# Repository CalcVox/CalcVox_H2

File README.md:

# CalcVox H2 Schematics and PCB Files

[View in Browser](https://kicanvas.org/?github=https://github.com/CalcVox/CalcVox_H2)

This is part of the [CalcVox](https://calcvox.org) Project. I am using KiCAD for these but I have included images below. 

I am trying to make these accessible but am struggling. If you know how to please open an issue.

## Parts

* [Teensy 4.1](https://www.pjrc.com/store/teensy41.html)
* [Seed Studio XIAO ESP32S3](https://www.seeedstudio.com/XIAO-ESP32S3-p-5627.html)
* [Adafruit UDA1334A I2S DAC (using a knockoff from amazon)](https://www.amazon.com/AITRIP-CJMCU-1334-UDA1334A-Decoder-Arduino/dp/B09DG21C7G)
* [Adafruit MiniBoost](https://www.adafruit.com/product/4654)
* [Rotary Encoder](https://www.sparkfun.com/products/9117)
* [Speaker (can use any)](https://www.adafruit.com/product/1891)
* 102AH 2.1mm Barrel Jack
* 3524N 3.5mm Audio Jack
* Piezo Buzzer
* Standard footprint buttons
* Various resistors
* Diodes

## Schematic

## PCB

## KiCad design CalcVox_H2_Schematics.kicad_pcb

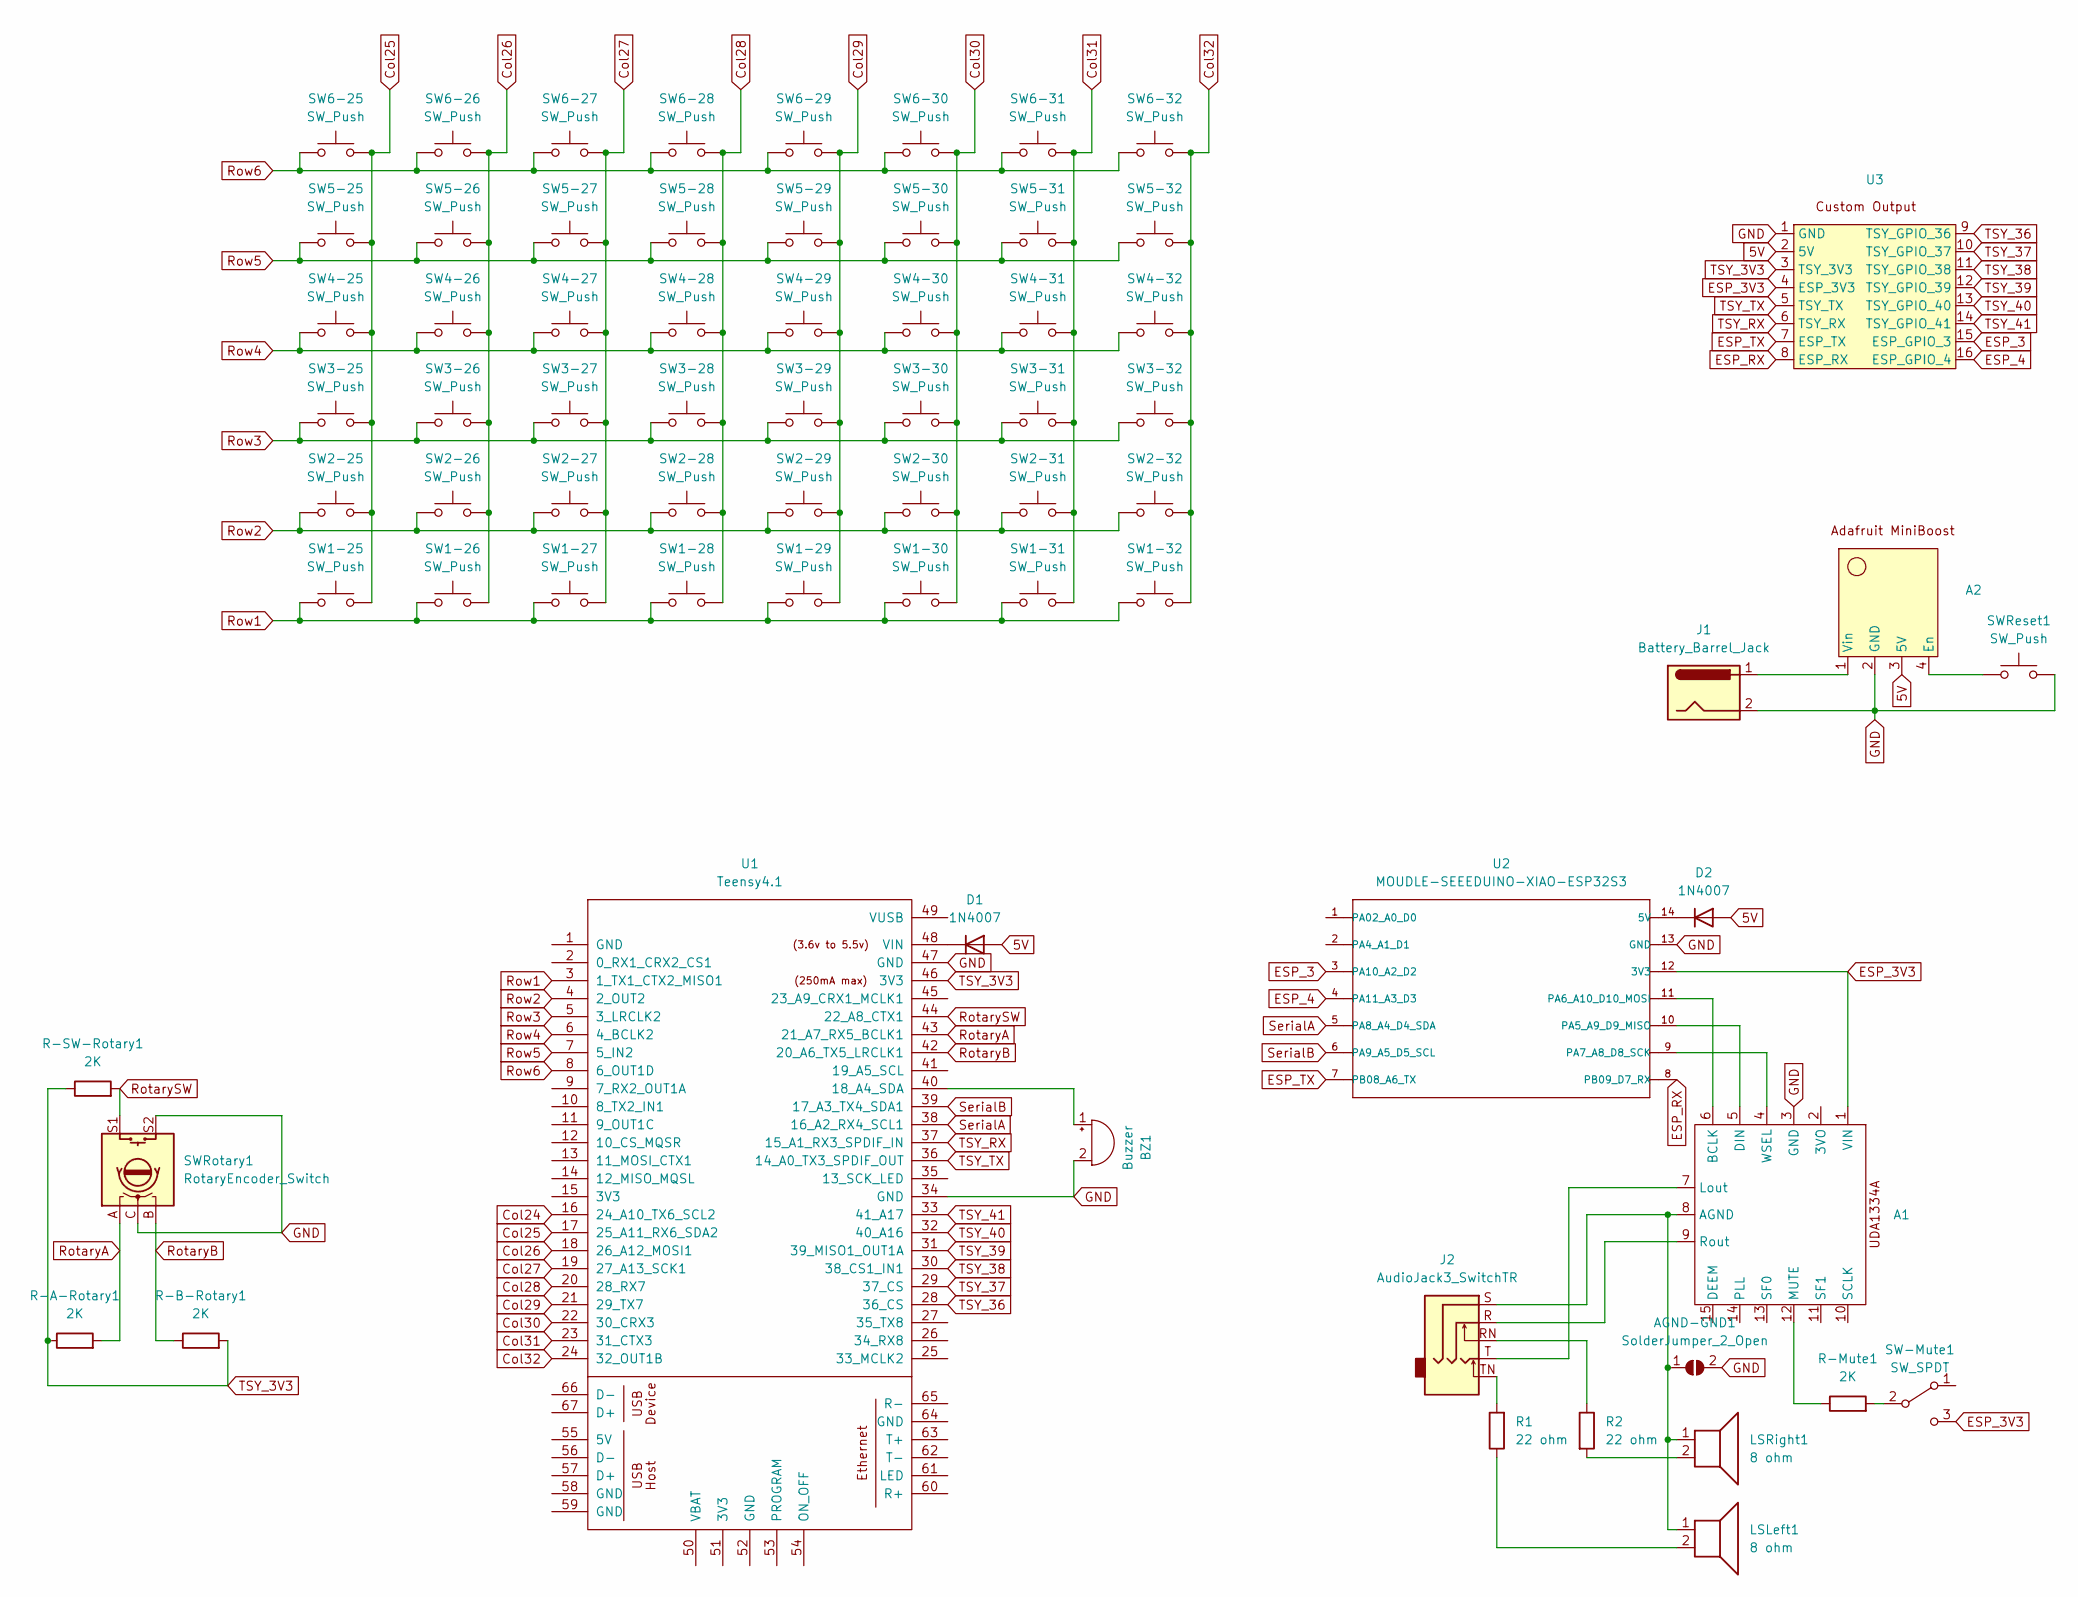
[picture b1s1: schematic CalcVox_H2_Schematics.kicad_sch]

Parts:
A1: Adafruit UDA1334A I2S Stereo DAC
A2: Adafruit MiniBost
AGND-GND1: SolderJumper_2_Open; SolderJumper-2_P1.3mm_Open_TrianglePad1.0x1.5mm
BZ1: Buzzer; Buzzer_12x9.5RM7.6
D1, D2: 1N4007; D_DO-41_SOD81_P10.16mm_Horizontal
J1: Battery_Barrel_Jack; BarrelJack_CUI_PJ-102AH_Horizontal
J2: AudioJack3_SwitchTR; Jack_3.5mm_CUI_SJ1-3524N_Horizontal
LSLeft1: 8 ohm; Speaker Hole
LSRight1: 8 ohm; Speaker Hole
R1, R2: 22 ohm; R_Axial_DIN0617_L17.0mm_D6.0mm_P25.40mm_Horizontal
R-A-Rotary1: 2K; R_Axial_DIN0207_L6.3mm_D2.5mm_P10.16mm_Horizontal
R-B-Rotary1: 2K; R_Axial_DIN0207_L6.3mm_D2.5mm_P10.16mm_Horizontal
R-Mute1: 2K; R_Axial_DIN0207_L6.3mm_D2.5mm_P10.16mm_Horizontal
R-SW-Rotary1: 2K; R_Axial_DIN0207_L6.3mm_D2.5mm_P10.16mm_Horizontal
SW1-25, SW1-26, SW1-27, SW1-28, SW1-29, SW1-30, SW1-31, SW1-32, SW2-25, SW2-26, SW2-27, SW2-28, SW2-29, SW2-30, SW2-31, SW2-32, SW3-25, SW3-26, SW3-27, SW3-28, SW3-29, SW3-30, SW3-31, SW3-32, SW4-25, SW4-26, SW4-27, SW4-28, SW4-29, SW4-30, SW4-31, SW4-32, SW5-25, SW5-26, SW5-27, SW5-28, SW5-29, SW5-30, SW5-31, SW5-32, SW6-25, SW6-26, SW6-27, SW6-28, SW6-29, SW6-30, SW6-31, SW6-32: SW_Push; SW_PUSH_6mm_H9.5mm
SW-Mute1: SW_SPDT; SW_Slide_1P2T_CK_OS102011MS2Q
SWReset1: SW_Push; SW_PUSH_6mm_H9.5mm
SWRotary1: RotaryEncoder_Switch; SF-ROTARY-ENCODER
U1: Teensy4.1; Teensy41
U2: MOUDLE-SEEEDUINO-XIAO-ESP32S3; MOUDLE14P-SMD-2.54-21X17.8MM
U3: Custom Output

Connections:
5V: A2.3 (5V), D1.2 (A), D2.2 (A), U3.2 (5V)
Col24: U1.16 (24_A10_TX6_SCL2)
Col25: SW1-25.2, SW2-25.2, SW3-25.2, SW4-25.2, SW5-25.2, SW6-25.2, U1.17 (25_A11_RX6_SDA2)
Col26: SW1-26.2, SW2-26.2, SW3-26.2, SW4-26.2, SW5-26.2, SW6-26.2, U1.18 (26_A12_MOSI1)
Col27: SW1-27.2, SW2-27.2, SW3-27.2, SW4-27.2, SW5-27.2, SW6-27.2, U1.19 (27_A13_SCK1)
Col28: SW1-28.2, SW2-28.2, SW3-28.2, SW4-28.2, SW5-28.2, SW6-28.2, U1.20 (28_RX7)
Col29: SW1-29.2, SW2-29.2, SW3-29.2, SW4-29.2, SW5-29.2, SW6-29.2, U1.21 (29_TX7)
Col30: SW1-30.2, SW2-30.2, SW3-30.2, SW4-30.2, SW5-30.2, SW6-30.2, U1.22 (30_CRX3)
Col31: SW1-31.2, SW2-31.2, SW3-31.2, SW4-31.2, SW5-31.2, SW6-31.2, U1.23 (31_CTX3)
Col32: SW1-32.2, SW2-32.2, SW3-32.2, SW4-32.2, SW5-32.2, SW6-32.2, U1.24 (32_OUT1B)
ESP_3: U2.3 (PA10_A2_D2), U3.15 (ESP_GPIO_3)
ESP_3V3: A1.1 (VIN), SW-Mute1.3 (C), U2.12 (3V3), U3.4 (ESP_3V3)
ESP_4: U2.4 (PA11_A3_D3), U3.16 (ESP_GPIO_4)
ESP_RX: U2.8 (PB09_D7_RX), U3.8 (ESP_RX)
ESP_TX: U2.7 (PB08_A6_TX), U3.7 (ESP_TX)
GND: A1.3 (GND), A2.2 (GND), AGND-GND1.2 (B), BZ1.2 (+), J1.2, SWReset1.2, SWRotary1.C, SWRotary1.S2, U1.34 (GND), U1.47 (GND), U2.13 (GND), U3.1 (GND)
unnamed: A1.8 (AGND), AGND-GND1.1 (A), J2.S, LSLeft1.1, LSRight1.1
unnamed: A1.6 (BCLK), U2.11 (PA6_A10_D10_MOSI)
unnamed: A1.5 (DIN), U2.10 (PA5_A9_D9_MISO)
unnamed: A1.7 (Lout), J2.T
unnamed: A1.12 (MUTE), R-Mute1.1
unnamed: A1.9 (Rout), J2.R
unnamed: A1.4 (WSEL), U2.9 (PA7_A8_D8_SCK)
unnamed: A2.4 (En), SWReset1.1
unnamed: A2.1 (Vin), J1.1
unnamed: BZ1.1 (-), U1.40 (18_A4_SDA)
unnamed: D1.1 (K), U1.48 (VIN)
unnamed: D2.1 (K), U2.14 (5V)
unnamed: J2.RN, R2.1
unnamed: J2.TN, R1.2
unnamed: LSLeft1.2, R1.1
unnamed: LSRight1.2, R2.2
unnamed: R-Mute1.2, SW-Mute1.2 (B)
RotaryA: R-A-Rotary1.2, SWRotary1.A, U1.43 (21_A7_RX5_BCLK1)
RotaryB: R-B-Rotary1.1, SWRotary1.B, U1.42 (20_A6_TX5_LRCLK1)
RotarySW: R-SW-Rotary1.2, SWRotary1.S1, U1.44 (22_A8_CTX1)
Row1: SW1-25.1, SW1-26.1, SW1-27.1, SW1-28.1, SW1-29.1, SW1-30.1, SW1-31.1, SW1-32.1, U1.3 (1_TX1_CTX2_MISO1)
Row2: SW2-25.1, SW2-26.1, SW2-27.1, SW2-28.1, SW2-29.1, SW2-30.1, SW2-31.1, SW2-32.1, U1.4 (2_OUT2)
Row3: SW3-25.1, SW3-26.1, SW3-27.1, SW3-28.1, SW3-29.1, SW3-30.1, SW3-31.1, SW3-32.1, U1.5 (3_LRCLK2)
Row4: SW4-25.1, SW4-26.1, SW4-27.1, SW4-28.1, SW4-29.1, SW4-30.1, SW4-31.1, SW4-32.1, U1.6 (4_BCLK2)
Row5: SW5-25.1, SW5-26.1, SW5-27.1, SW5-28.1, SW5-29.1, SW5-30.1, SW5-31.1, SW5-32.1, U1.7 (5_IN2)
Row6: SW6-25.1, SW6-26.1, SW6-27.1, SW6-28.1, SW6-29.1, SW6-30.1, SW6-31.1, SW6-32.1, U1.8 (6_OUT1D)
SerialA: U1.38 (16_A2_RX4_SCL1), U2.5 (PA8_A4_D4_SDA)
SerialB: U1.39 (17_A3_TX4_SDA1), U2.6 (PA9_A5_D5_SCL)
TSY_3V3: R-A-Rotary1.1, R-B-Rotary1.2, R-SW-Rotary1.1, U1.46 (3V3), U3.3 (TSY_3V3)
TSY_36: U1.28 (36_CS), U3.9 (TSY_GPIO_36)
TSY_37: U1.29 (37_CS), U3.10 (TSY_GPIO_37)
TSY_38: U1.30 (38_CS1_IN1), U3.11 (TSY_GPIO_38)
TSY_39: U1.31 (39_MISO1_OUT1A), U3.12 (TSY_GPIO_39)
TSY_40: U1.32 (40_A16), U3.13 (TSY_GPIO_40)
TSY_41: U1.33 (41_A17), U3.14 (TSY_GPIO_41)
TSY_RX: U1.37 (15_A1_RX3_SPDIF_IN), U3.6 (TSY_RX)
TSY_TX: U1.36 (14_A0_TX3_SPDIF_OUT), U3.5 (TSY_TX)

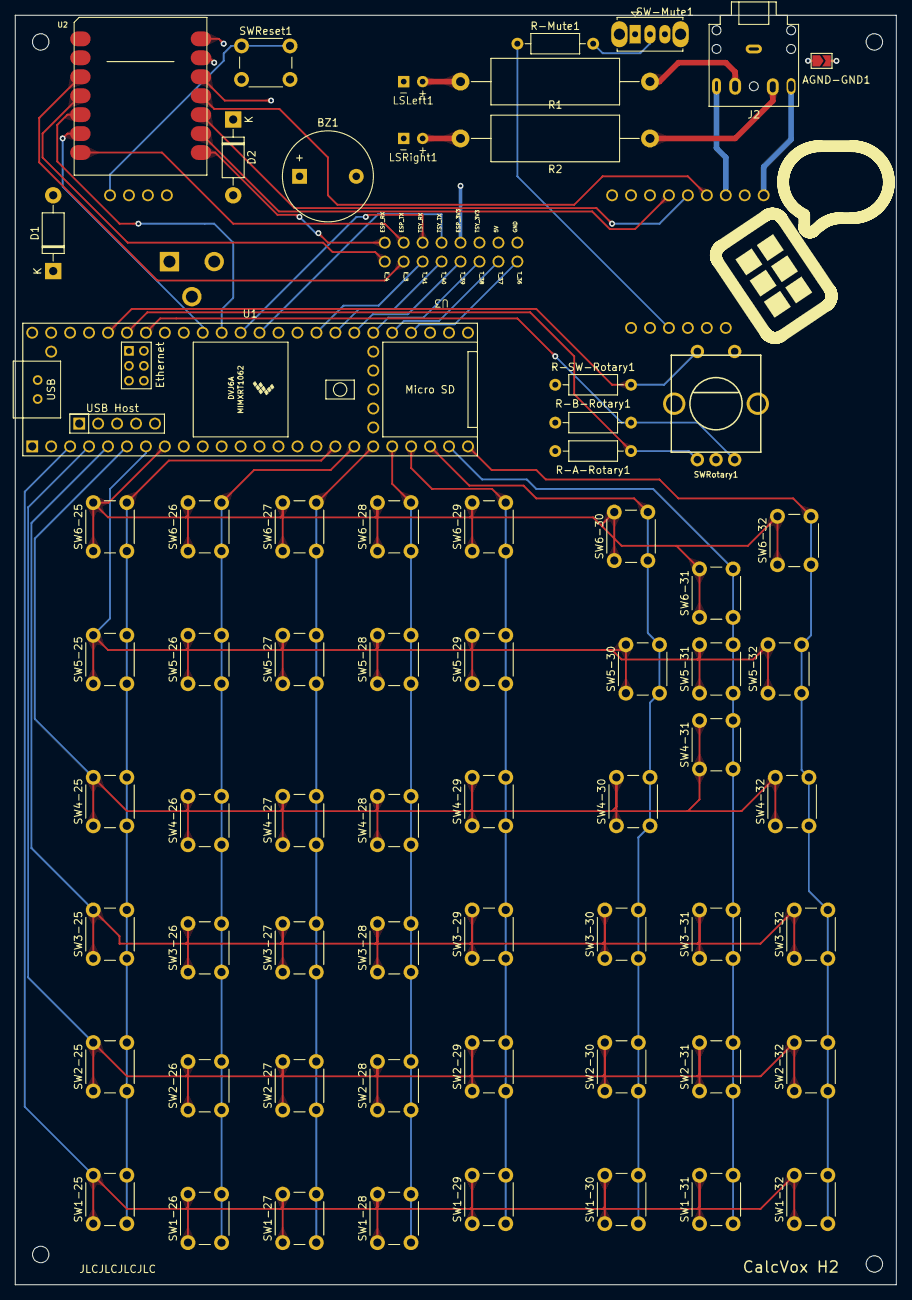
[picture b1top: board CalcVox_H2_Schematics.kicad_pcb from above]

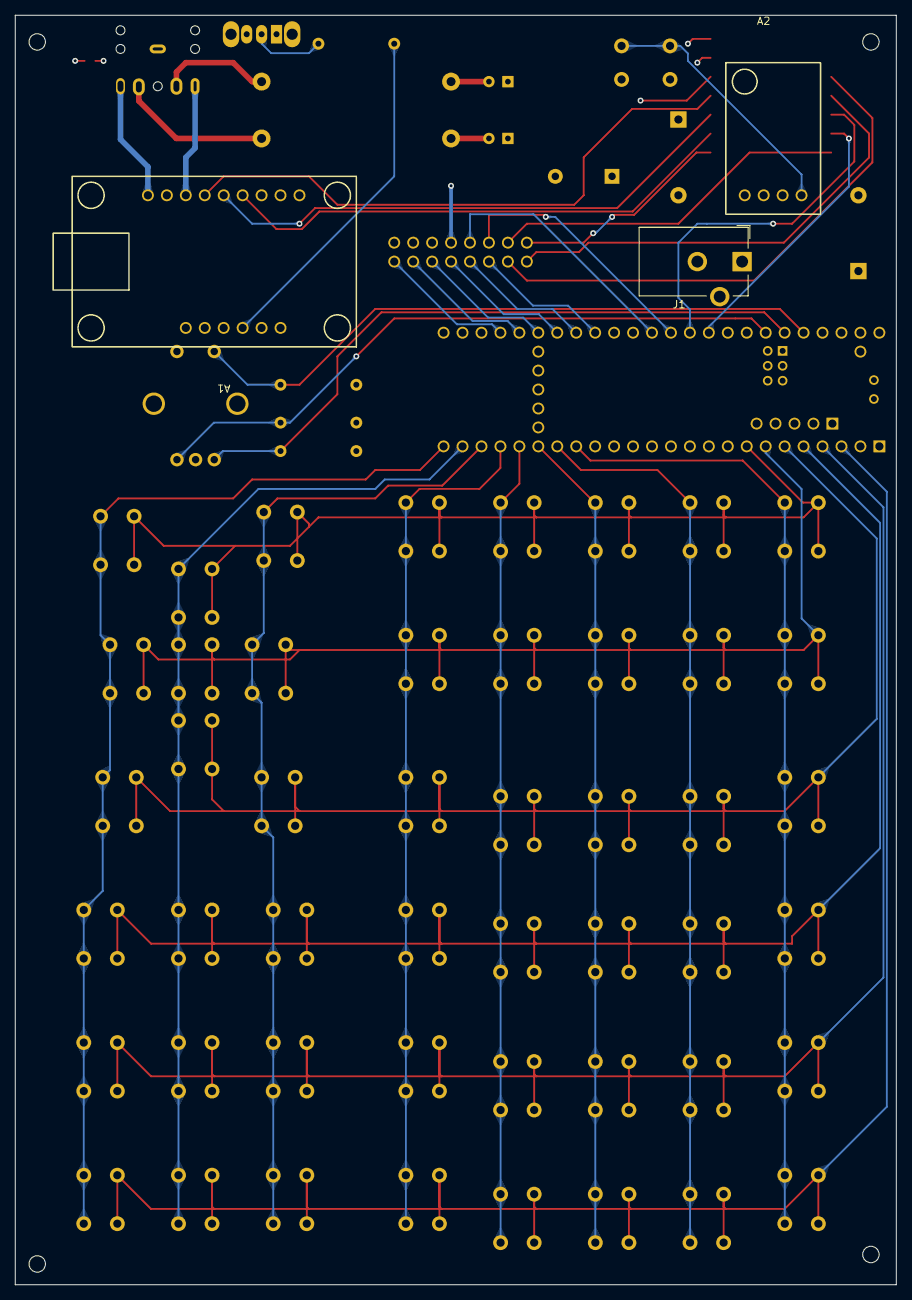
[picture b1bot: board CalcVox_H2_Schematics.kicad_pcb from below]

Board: 4 copper layers, 118.1 x 170.2 mm, 70 parts (3 on the bottom side), 52 nets.

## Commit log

2024-02-14 fixed gitignore
2024-02-14 removed files
2024-02-14 Small change to move board up
2024-02-15 added readme
2024-02-15 oops
2024-03-06 Added 3d models and fixed small mistakes
2024-03-08 updated with feedback
